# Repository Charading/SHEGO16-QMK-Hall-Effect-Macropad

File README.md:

# SHEGO16-QMK-Hall-Effect-Macropad
An RP2040-powered 4x4 15 key macropad with a knob on the top row, that runs custom QMK firmware that allows analogue hall effect sensors to work, also has SOCD, works with VIA and SignalRGB

### Features
- QMK Firmware
- VIA Compatible
- Hall effect (adjustable actuation also)
- SOCD (last input wins on A and D)
- Works with SignalRGB
- ST7735 TFT Screen *(currently disabled/broken due to complications and implementing another way)*
- Per-key RGB
- Ambient strip
- Custom keycodes to send to UART to control esp32 *(for tft screen on my future build)* etc
- Multiple GPIO broken out for testing purposes
- Blink LED on GPIO25

I cant find a Hall effect keyboard that i genuinely like that has all the features that i want so i thought to make one myself. Technically i am still in prototype phase for the 'endgame' board i yearn to have, this was a originally a little test board that I was making so I could figure out how to do firmware. I've been working months on end on this project with many pcbs and components surrounding me. The end goal is a 75% keyboard, knob, a tft screen that can play gifs, **north** facing RGB (my goodness i hate south facing), and magnetic switches with socd. Sadly I think it would be too difficult to create a software/web utility to control certain features of the board so thats why after weeks on end trying to build firmware from scratch with C, then scrapped that and tried Rust, then scrapped again and thought to use heavily edited qmk, i am now here.
For my big 75%, the screen will now be implemented by using an [ESP32 running a GIF decoder](https://github.com/Charading/ESP32-GIF-Player ) that accepts UART commands and it uses SD card for storage

Thankyou [riskable](https://github.com/riskable)  for your amazing resources and being my inspiration for this passion project. 

This was one of my first ever pcbs

I recommend using [this version](https://github.com/Charading/qmk_picosdk
) of qmk for easy building of firmware, i could not get pico/stdlib.h to be located at all with normal qmk_firmware :(.

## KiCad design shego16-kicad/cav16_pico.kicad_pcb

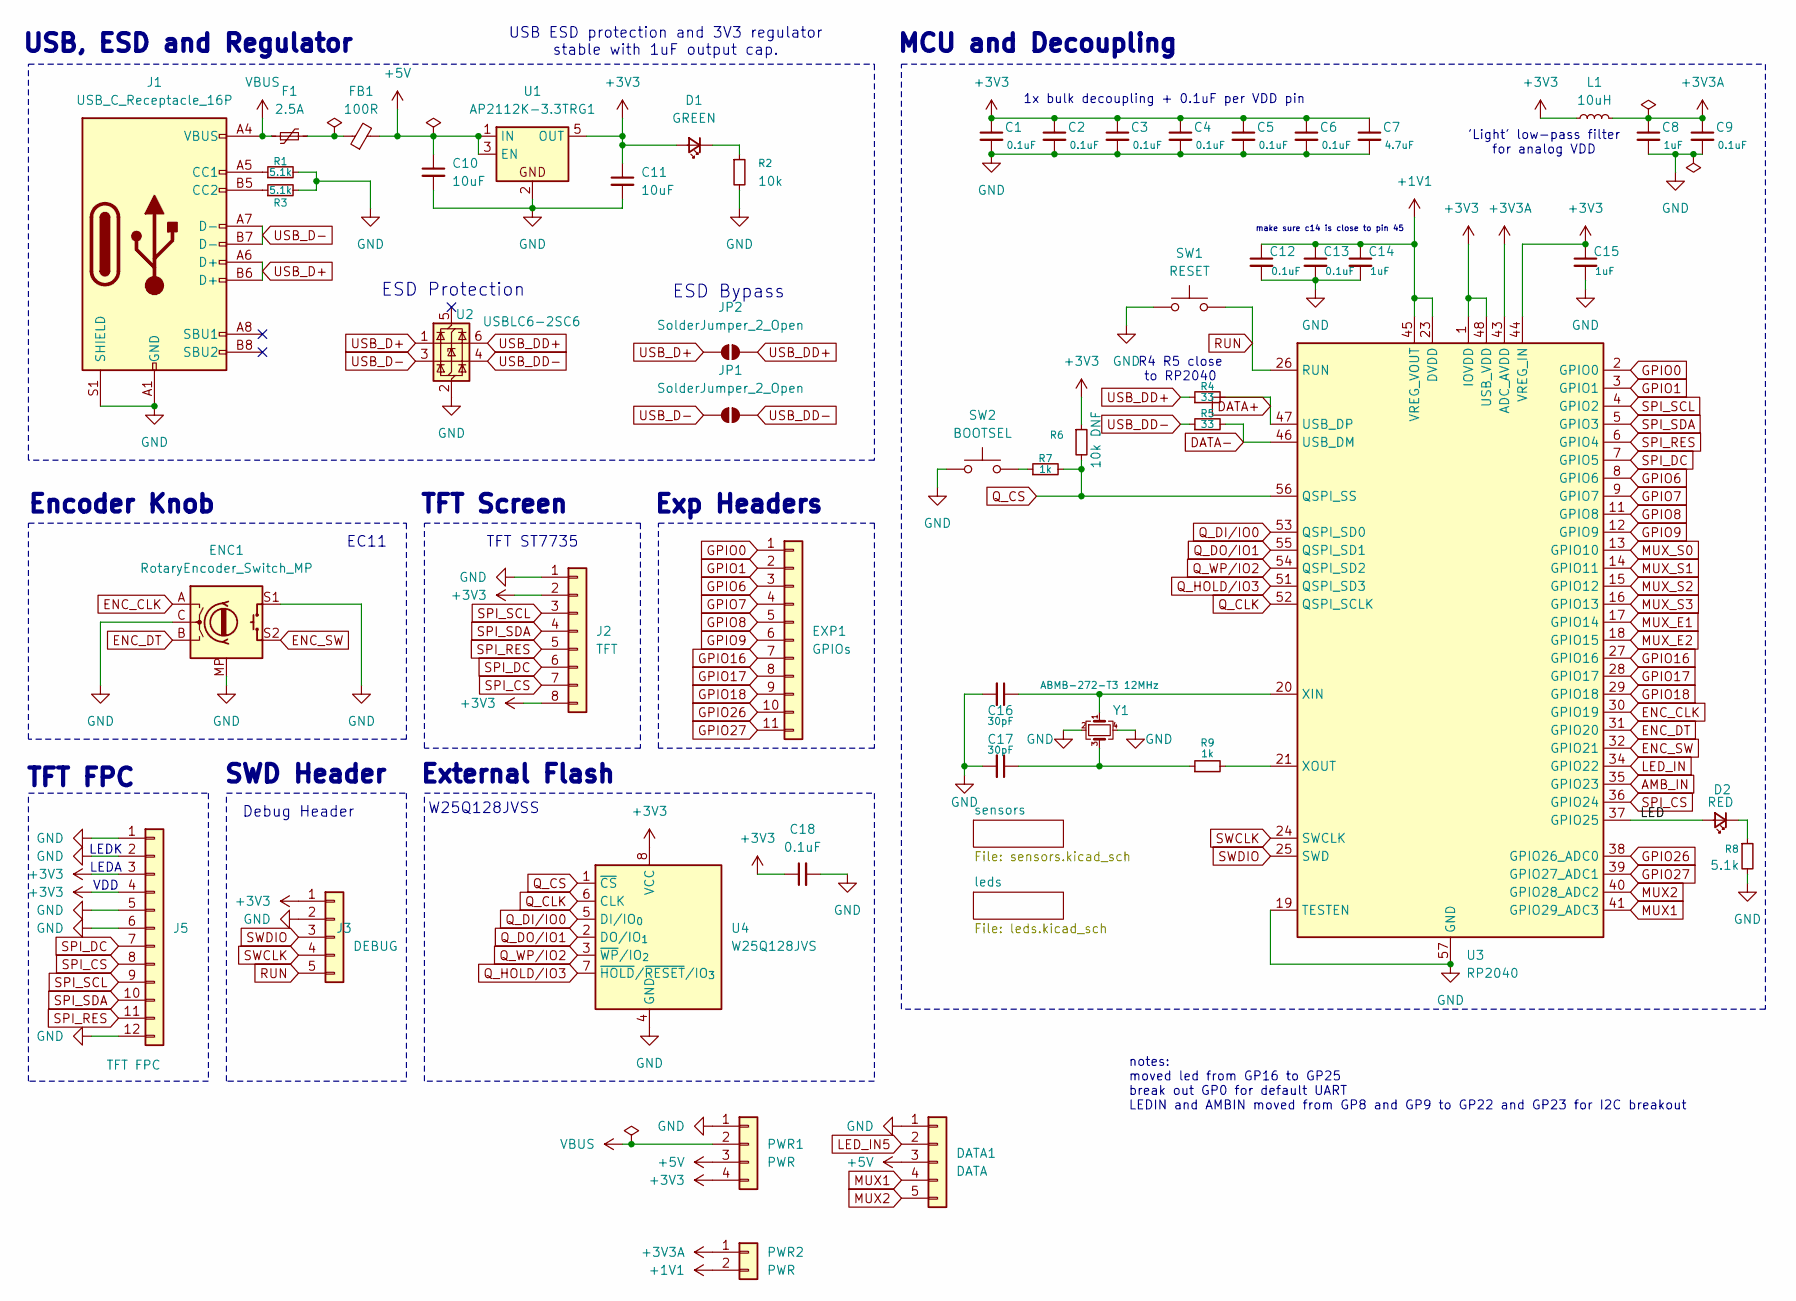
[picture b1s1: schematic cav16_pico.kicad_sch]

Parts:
C1, C2, C3, C4, C5, C6, C9, C12, C13, C18: 0.1uF; C_0402_1005Metric_Pad0.74x0.62mm_HandSolder
C7: 4.7uF; C_0805_2012Metric_Pad1.18x1.45mm_HandSolder
C8, C14, C15: 1uF; C_0402_1005Metric_Pad0.74x0.62mm_HandSolder
C10, C11: 10uF; C_0805_2012Metric_Pad1.18x1.45mm_HandSolder
C16, C17: 30pF; C_0402_1005Metric_Pad0.74x0.62mm_HandSolder
D1: GREEN; LED_0805_2012Metric_Pad1.15x1.40mm_HandSolder
D2: RED; LED_0805_2012Metric_Pad1.15x1.40mm_HandSolder
DATA1: DATA; PinHeader_1x05_P2.54mm_Vertical
ENC1: RotaryEncoder_Switch_MP; RotaryEncoder_Alps_EC11E-Switch_Vertical_H20mm_CircularMoun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
EXP1: GPIOs; PinHeader_1x11_P2.54mm_Vertical
F1: 2.5A; Fuse_1206_3216Metric_Pad1.42x1.75mm_BigPads
FB1: 100R; Ferrite_0805_2012Metric_Pad1.05x1.20mm_BigPads
J1: USB_C_Receptacle_16P; USB_C_Receptacle_HRO_TYPE-C-31-M-12
J2: TFT; PinHeader_1x08_P2.54mm_Vertical
J3: DEBUG; PinHeader_1x05_P2.54mm_Vertical
J5: TFT FPC; Hirose_FH12-12S-0.5SH_1x12-1MP_P0.50mm_Horizontal
JP1, JP2: SolderJumper_2_Open; SolderJumper-2_P1.3mm_Open_TrianglePad1.0x1.5mm
L1: 10uH; L_0805_2012Metric_Pad1.15x1.40mm_HandSolder
PWR1: PWR; PinHeader_1x04_P2.54mm_Vertical
PWR2: PWR; PinHeader_1x02_P2.54mm_Vertical
R1, R3: 5.1k; R_0603_1608Metric_Pad0.98x0.95mm_HandSolder
R2: 10k; R_0805_2012Metric_Pad1.20x1.40mm_HandSolder
R4, R5: 33; R_0805_2012Metric_Pad1.20x1.40mm_HandSolder
R6: 10k DNF; R_0603_1608Metric_Pad0.98x0.95mm_HandSolder
R7: 1k; R_0603_1608Metric_Pad0.98x0.95mm_HandSolder
R8: 5.1k; R_0805_2012Metric_Pad1.20x1.40mm_HandSolder
R9: 1k; C_0402_1005Metric_Pad0.74x0.62mm_HandSolder
SW1: RESET; SW_SPST_PTS810
SW2: BOOTSEL; SW_SPST_PTS810
U1: AP2112K-3.3TRG1; SOT-23-5
U2: USBLC6-2SC6; SOT-23-6
U3: RP2040; QFN-56-1EP_7x7mm_P0.4mm_EP3.2x3.2mm_ThermalVias
U4: W25Q128JVS; SOIC-8_5.3x5.3mm_P1.27mm
Y1: ABMB-272-T3 12MHz; Crystal_SMD_3225-4Pin_3.2x2.5mm_BigPads

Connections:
+1V1: C12.1, C13.1, C14.1, PWR2.2, U3.23 (DVDD), U3.45 (VREG_VOUT), U3.50 (DVDD)
+3V3: C1.1, C2.1, C3.1, C4.1, C5.1, C6.1, C7.1, C11.1, C15.1, C18.1, D1.2 (A), J2.2, J2.8, J3.1, J5.3, J5.4, L1.1, PWR1.4, R6.1, U1.5 (OUT), U3.1 (IOVDD), U3.10 (IOVDD), U3.22 (IOVDD), U3.33 (IOVDD), U3.42 (IOVDD), U3.44 (VREG_IN), U3.48 (USB_VDD), U3.49 (IOVDD), U4.8 (VCC); also elsewhere on the board
+3V3A: C8.1, C9.1, L1.2, PWR2.1, U3.43 (ADC_AVDD)
+5V: C10.1, DATA1.3, FB1.2, PWR1.3, U1.1 (IN), U1.3 (EN); also elsewhere on the board
/LED: D2.2 (A), U3.37 (GPIO25)
AMB_IN: U3.35 (GPIO23); also elsewhere on the board
DATA+: R4.2, U3.47 (USB_DP)
DATA-: R5.2, U3.46 (USB_DM)
ENC_CLK: ENC1.A, U3.30 (GPIO19)
ENC_DT: ENC1.B, U3.31 (GPIO20)
ENC_SW: ENC1.S2, U3.32 (GPIO21)
GND: C1.2, C2.2, C3.2, C4.2, C5.2, C6.2, C7.2, C8.2, C9.2, C10.2, C11.2, C12.2, C13.2, C14.2, C15.2, C16.2, C17.2, C18.2, DATA1.1, ENC1.C, ENC1.MP, ENC1.S1, J1.A1 (GND), J1.A12 (GND), J1.B1 (GND), J1.B12 (GND), J1.S1 (SHIELD), J2.1, J3.2, J5.1, J5.2, J5.5, J5.6, J5.12, J5.MP, PWR1.1, R1.2, R2.2, R3.2, R8.2, SW1.1, SW2.1, U1.2, U2.2 (GND), U3.19 (TESTEN), U3.57 (GND), U4.4 (GND), Y1.2, Y1.4; also elsewhere on the board
GPIO0: EXP1.1, U3.2 (GPIO0)
GPIO1: EXP1.2, U3.3 (GPIO1)
GPIO6: EXP1.3, U3.8 (GPIO6)
GPIO7: EXP1.4, U3.9 (GPIO7)
GPIO8: EXP1.5, U3.11 (GPIO8)
GPIO9: EXP1.6, U3.12 (GPIO9)
GPIO16: EXP1.7, U3.27 (GPIO16)
GPIO17: EXP1.8, U3.28 (GPIO17)
GPIO18: EXP1.9, U3.29 (GPIO18)
GPIO26: EXP1.10, U3.38 (GPIO26_ADC0)
GPIO27: EXP1.11, U3.39 (GPIO27_ADC1)
LED_IN: U3.34 (GPIO22); also elsewhere on the board
LED_IN5: DATA1.2; also elsewhere on the board
MUX1: DATA1.4, U3.41 (GPIO29_ADC3); also elsewhere on the board
MUX2: DATA1.5, U3.40 (GPIO28_ADC2); also elsewhere on the board
MUX_E1: U3.17 (GPIO14); also elsewhere on the board
MUX_E2: U3.18 (GPIO15); also elsewhere on the board
MUX_S0: U3.13 (GPIO10); also elsewhere on the board
MUX_S1: U3.14 (GPIO11); also elsewhere on the board
MUX_S2: U3.15 (GPIO12); also elsewhere on the board
MUX_S3: U3.16 (GPIO13); also elsewhere on the board
unnamed: C17.1, R9.1, Y1.3
unnamed: D1.1 (K), R2.1
unnamed: D2.1 (K), R8.1
unnamed: F1.2, FB1.1
unnamed: J1.A5 (CC1), R1.1
unnamed: J1.B5 (CC2), R3.1
unnamed: R7.1, SW2.2
unnamed: C16.1, U3.20 (XIN), Y1.1
unnamed: R9.2, U3.21 (XOUT)
Q_CLK: U3.52 (QSPI_SCLK), U4.6 (CLK)
Q_CS: R6.2, R7.2, U3.56 (QSPI_SS), U4.1 (~CS)
Q_DI/IO0: U3.53 (QSPI_SD0), U4.5 (DI/IO_{0})
Q_DO/IO1: U3.55 (QSPI_SD1), U4.2 (DO/IO_{1})
Q_HOLD/IO3: U3.51 (QSPI_SD3), U4.7 (~HOLD/~RESET/IO_{3})
Q_WP/IO2: U3.54 (QSPI_SD2), U4.3 (~WP/IO_{2})
RUN: J3.5, SW1.2, U3.26 (RUN)
SPI_CS: J2.7, J5.8, U3.36 (GPIO24)
SPI_DC: J2.6, J5.7, U3.7 (GPIO5)
SPI_RES: J2.5, J5.11, U3.6 (GPIO4)
SPI_SCL: J2.3, J5.9, U3.4 (GPIO2)
SPI_SDA: J2.4, J5.10, U3.5 (GPIO3)
SWCLK: J3.4, U3.24 (SWCLK)
SWDIO: J3.3, U3.25 (SWD)
USB_D+: J1.A6 (D+), J1.B6 (D+), JP2.1 (A), U2.1 (I/O1)
USB_D-: J1.A7 (D-), J1.B7 (D-), JP1.1 (A), U2.3 (I/O2)
USB_DD+: JP2.2 (B), R4.1, U2.6 (I/O1)
USB_DD-: JP1.2 (B), R5.1, U2.4 (I/O2)
VBUS: F1.1, J1.A4 (VBUS), J1.A9 (VBUS), J1.B4 (VBUS), J1.B9 (VBUS), PWR1.2

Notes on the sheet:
TFT Screen
LEDA
R4 R5 close to RP2040
notes: moved led from GP16 to GP25 break out GP0 for default UART LEDIN and AMBIN moved from GP8 and GP9 to GP22 and GP23 for I2C breakout
Encoder Knob
MCU and Decoupling
LEDK
External Flash
USB, ESD and Regulator
ESD Bypass
SWD Header
make sure c14 is close to pin 45
'Light' low-pass filter for analog VDD
Debug Header
VDD
Exp Headers
EC11
1x bulk decoupling + 0.1uF per VDD pin
TFT FPC
ESD Protection
USB ESD protection and 3V3 regulator stable with 1uF output cap.
TFT ST7735
W25Q128JVSS

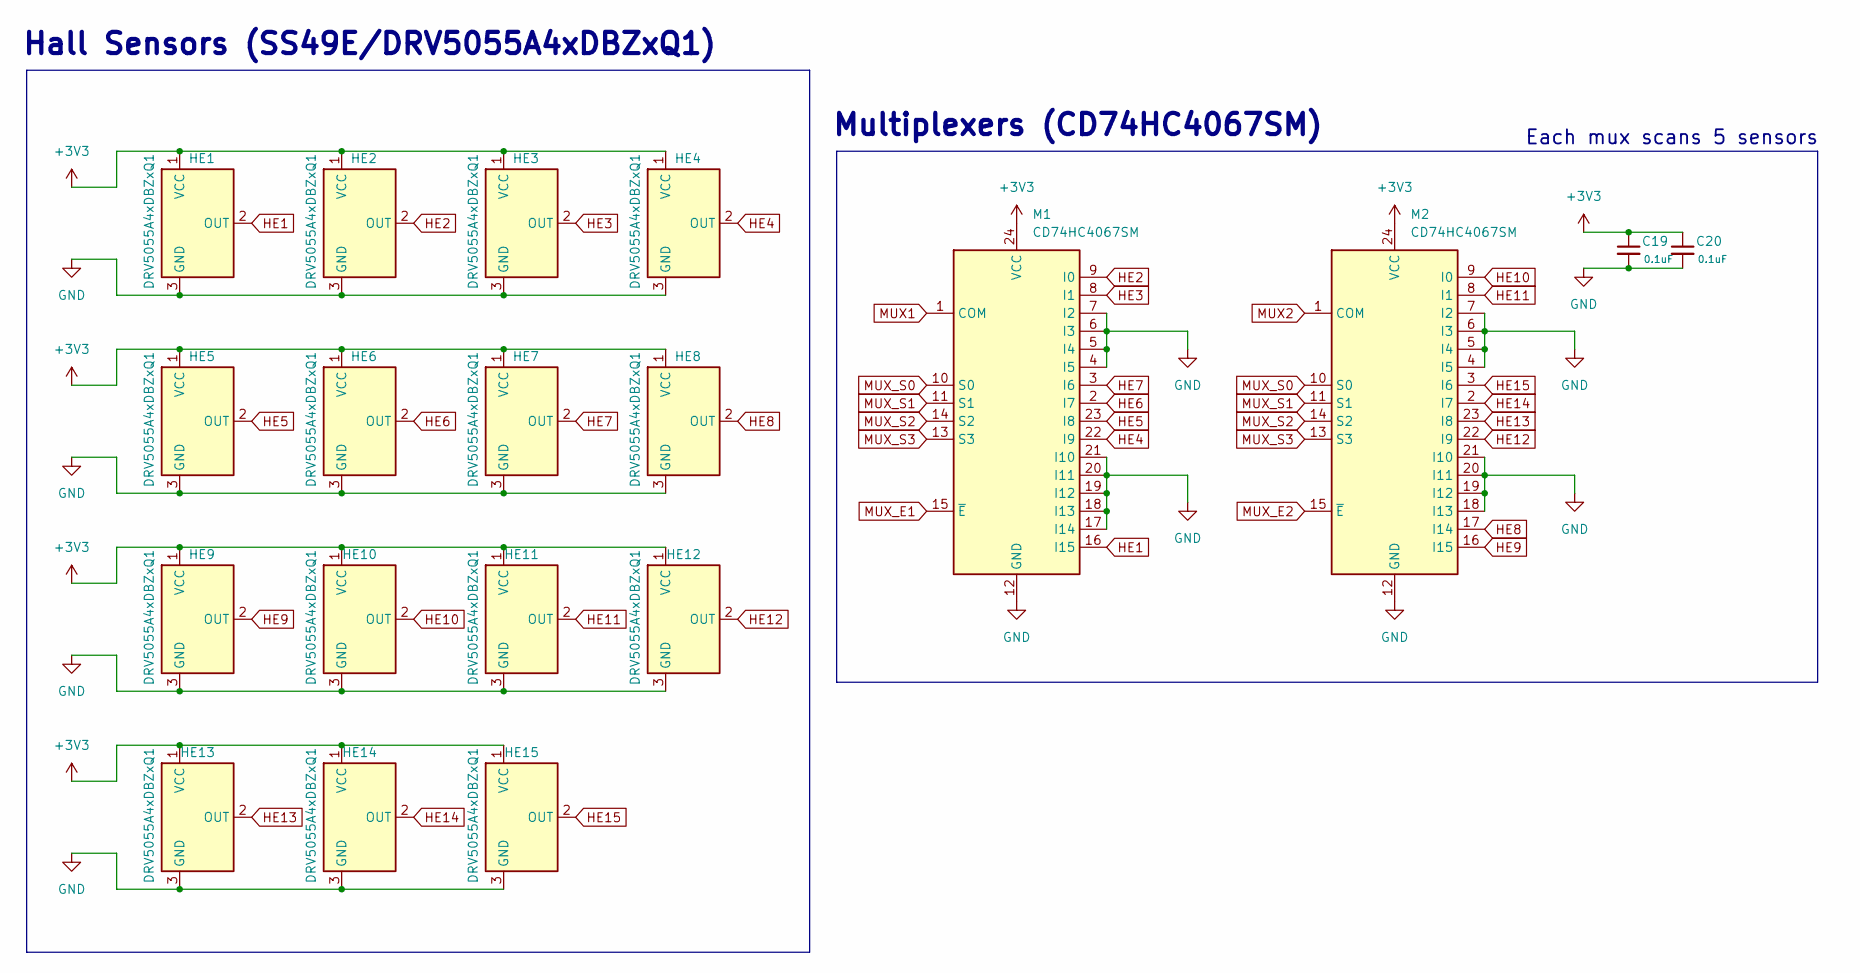
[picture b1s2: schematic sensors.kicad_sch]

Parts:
C19, C20: 0.1uF; C_0402_1005Metric_Pad0.74x0.62mm_HandSolder
HE1, HE2, HE3, HE4, HE5, HE6, HE7, HE8, HE9, HE10, HE11, HE12, HE13, HE14, HE15: DRV5055A4xDBZxQ1; SW_MX_HE_90deg_1u
M1, M2: CD74HC4067SM; SSOP-24_5.3x8.2mm_P0.65mm

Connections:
+3V3: C19.1, C20.1, HE1.1 (VCC), HE2.1 (VCC), HE3.1 (VCC), HE4.1 (VCC), HE5.1 (VCC), HE6.1 (VCC), HE7.1 (VCC), HE8.1 (VCC), HE9.1 (VCC), HE10.1 (VCC), HE11.1 (VCC), HE12.1 (VCC), HE13.1 (VCC), HE14.1 (VCC), HE15.1 (VCC), M1.24 (VCC), M2.24 (VCC); also elsewhere on the board
GND: C19.2, C20.2, HE1.3 (GND), HE2.3 (GND), HE3.3 (GND), HE4.3 (GND), HE5.3 (GND), HE6.3 (GND), HE7.3 (GND), HE8.3 (GND), HE9.3 (GND), HE10.3 (GND), HE11.3 (GND), HE12.3 (GND), HE13.3 (GND), HE14.3 (GND), HE15.3 (GND), M1.4 (I5), M1.5 (I4), M1.6 (I3), M1.7 (I2), M1.12 (GND), M1.17 (I14), M1.18 (I13), M1.19 (I12), M1.20 (I11), M1.21 (I10), M2.4 (I5), M2.5 (I4), M2.6 (I3), M2.7 (I2), M2.12 (GND), M2.18 (I13), M2.19 (I12), M2.20 (I11), M2.21 (I10); also elsewhere on the board
HE1: HE1.2 (OUT), M1.16 (I15)
HE2: HE2.2 (OUT), M1.9 (I0)
HE3: HE3.2 (OUT), M1.8 (I1)
HE4: HE4.2 (OUT), M1.22 (I9)
HE5: HE5.2 (OUT), M1.23 (I8)
HE6: HE6.2 (OUT), M1.2 (I7)
HE7: HE7.2 (OUT), M1.3 (I6)
HE8: HE8.2 (OUT), M2.17 (I14)
HE9: HE9.2 (OUT), M2.16 (I15)
HE10: HE10.2 (OUT), M2.9 (I0)
HE11: HE11.2 (OUT), M2.8 (I1)
HE12: HE12.2 (OUT), M2.22 (I9)
HE13: HE13.2 (OUT), M2.23 (I8)
HE14: HE14.2 (OUT), M2.2 (I7)
HE15: HE15.2 (OUT), M2.3 (I6)
MUX1: M1.1 (COM); also elsewhere on the board
MUX2: M2.1 (COM); also elsewhere on the board
MUX_E1: M1.15 (~E); also elsewhere on the board
MUX_E2: M2.15 (~E); also elsewhere on the board
MUX_S0: M1.10 (S0), M2.10 (S0); also elsewhere on the board
MUX_S1: M1.11 (S1), M2.11 (S1); also elsewhere on the board
MUX_S2: M1.14 (S2), M2.14 (S2); also elsewhere on the board
MUX_S3: M1.13 (S3), M2.13 (S3); also elsewhere on the board

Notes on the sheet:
Each mux scans 5 sensors
Multiplexers (CD74HC4067SM)
Hall Sensors (SS49E/DRV5055A4xDBZxQ1)

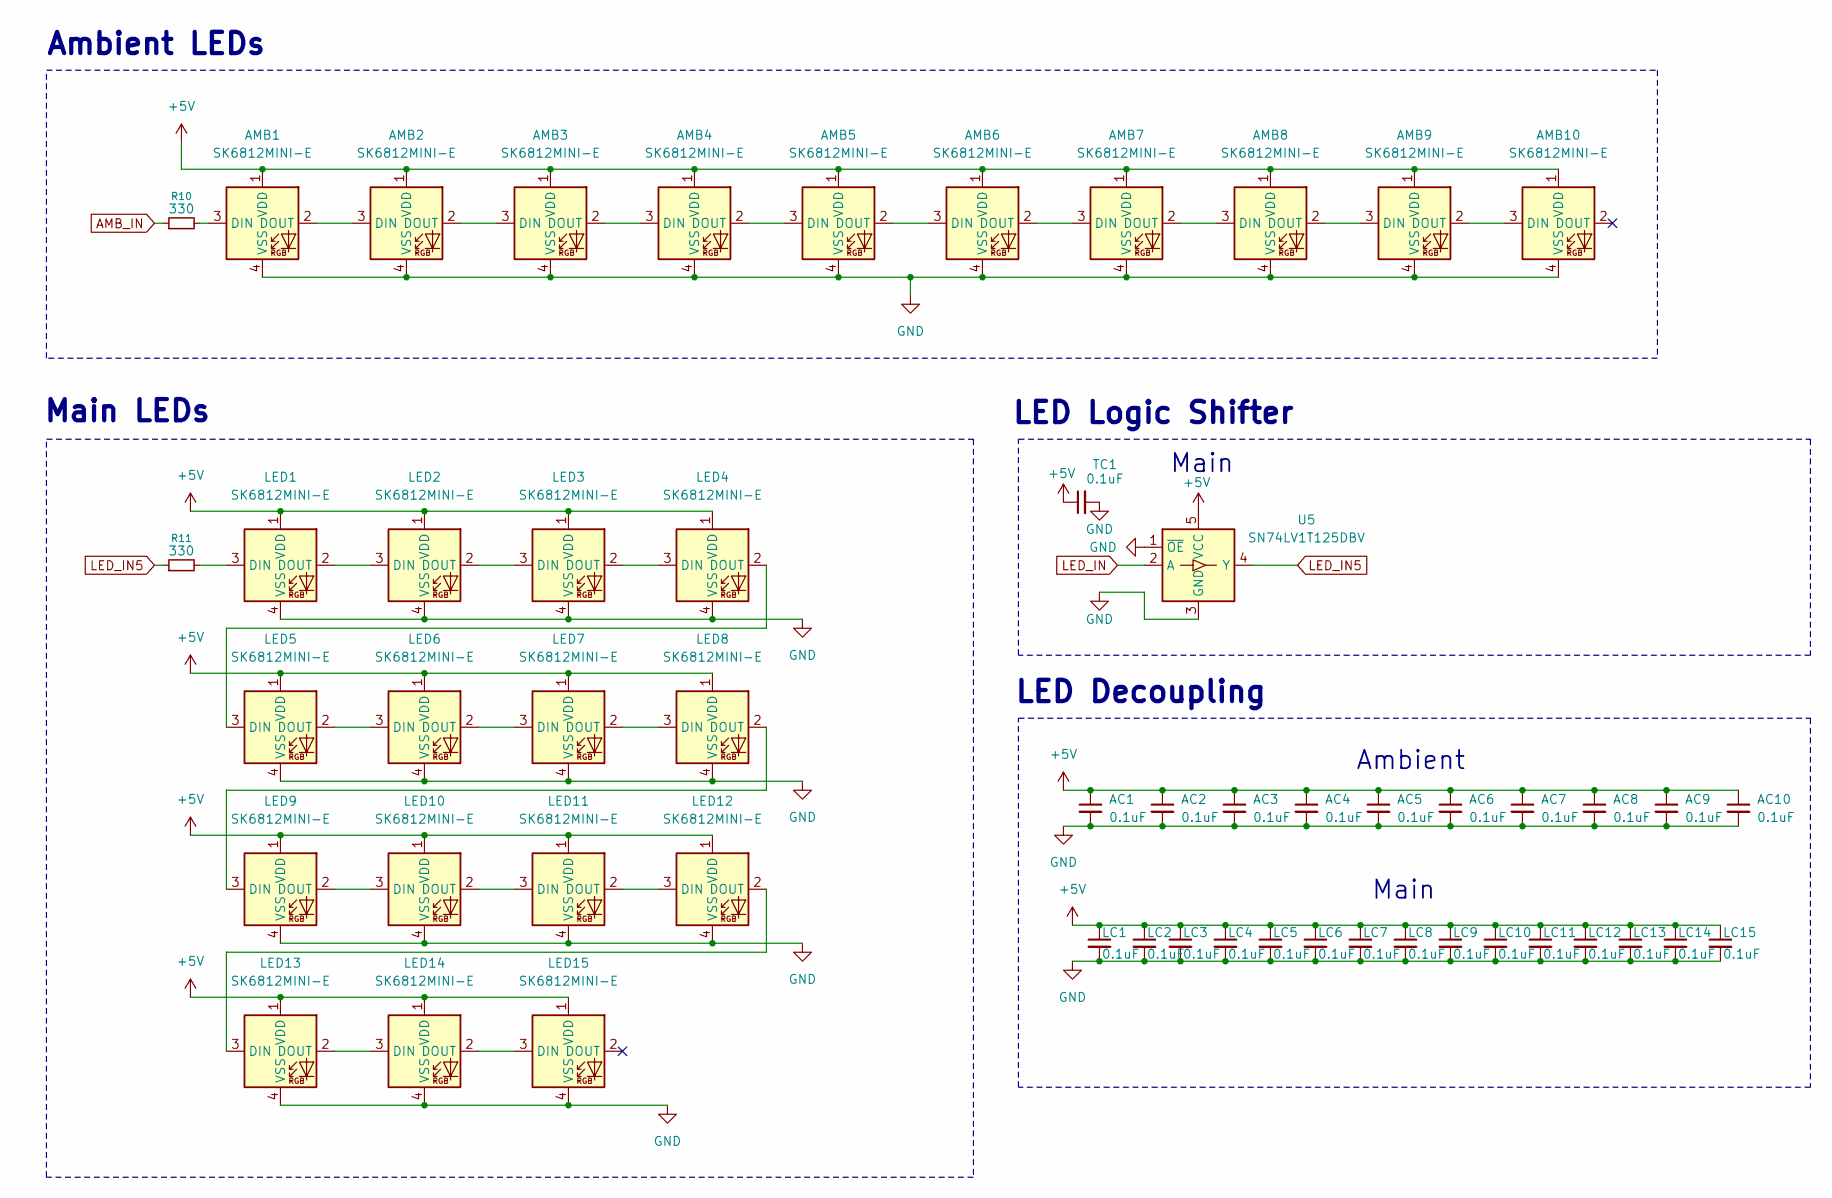
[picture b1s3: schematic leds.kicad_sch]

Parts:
AC1, AC2, AC3, AC4, AC5, AC6, AC7, AC8, AC9, AC10: 0.1uF; C_0805_2012Metric_Pad1.18x1.45mm_HandSolder
AMB1, AMB2, AMB3, AMB4, AMB5, AMB6, AMB7, AMB8, AMB9, AMB10: SK6812MINI-E; LED_6028R
LC1, LC2, LC3, LC4, LC5, LC6, LC7, LC8, LC9, LC10, LC11, LC12, LC13, LC14, LC15: 0.1uF; C_0805_2012Metric_Pad1.18x1.45mm_HandSolder
LED1, LED2, LED3, LED4, LED5, LED6, LED7, LED8, LED9, LED10, LED11, LED12, LED13, LED14, LED15: SK6812MINI-E; LED_6028R
R10, R11: 330; R_0603_1608Metric_Pad0.98x0.95mm_HandSolder
TC1: 0.1uF; C_0805_2012Metric_Pad1.18x1.45mm_HandSolder
U5: SN74LV1T125DBV; SOT-23-5

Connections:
+5V: AC1.1, AC2.1, AC3.1, AC4.1, AC5.1, AC6.1, AC7.1, AC8.1, AC9.1, AC10.1, AMB1.1 (VDD), AMB2.1 (VDD), AMB3.1 (VDD), AMB4.1 (VDD), AMB5.1 (VDD), AMB6.1 (VDD), AMB7.1 (VDD), AMB8.1 (VDD), AMB9.1 (VDD), AMB10.1 (VDD), LC1.1, LC2.1, LC3.1, LC4.1, LC5.1, LC6.1, LC7.1, LC8.1, LC9.1, LC10.1, LC11.1, LC12.1, LC13.1, LC14.1, LC15.1, LED1.1 (VDD), LED2.1 (VDD), LED3.1 (VDD), LED4.1 (VDD), LED5.1 (VDD), LED6.1 (VDD), LED7.1 (VDD), LED8.1 (VDD), LED9.1 (VDD), LED10.1 (VDD), LED11.1 (VDD), LED12.1 (VDD), LED13.1 (VDD), LED14.1 (VDD), LED15.1 (VDD), TC1.1, U5.5 (VCC); also elsewhere on the board
AMB_IN: R10.1; also elsewhere on the board
GND: AC1.2, AC2.2, AC3.2, AC4.2, AC5.2, AC6.2, AC7.2, AC8.2, AC9.2, AC10.2, AMB1.4 (VSS), AMB2.4 (VSS), AMB3.4 (VSS), AMB4.4 (VSS), AMB5.4 (VSS), AMB6.4 (VSS), AMB7.4 (VSS), AMB8.4 (VSS), AMB9.4 (VSS), AMB10.4 (VSS), LC1.2, LC2.2, LC3.2, LC4.2, LC5.2, LC6.2, LC7.2, LC8.2, LC9.2, LC10.2, LC11.2, LC12.2, LC13.2, LC14.2, LC15.2, LED1.4 (VSS), LED2.4 (VSS), LED3.4 (VSS), LED4.4 (VSS), LED5.4 (VSS), LED6.4 (VSS), LED7.4 (VSS), LED8.4 (VSS), LED9.4 (VSS), LED10.4 (VSS), LED11.4 (VSS), LED12.4 (VSS), LED13.4 (VSS), LED14.4 (VSS), LED15.4 (VSS), TC1.2, U5.1 (~OE), U5.3 (GND); also elsewhere on the board
LED_IN: U5.2 (A); also elsewhere on the board
LED_IN5: R11.1, U5.4 (Y); also elsewhere on the board
unnamed: AMB1.3 (DIN), R10.2
unnamed: AMB1.2 (DOUT), AMB2.3 (DIN)
unnamed: AMB2.2 (DOUT), AMB3.3 (DIN)
unnamed: AMB3.2 (DOUT), AMB4.3 (DIN)
unnamed: AMB4.2 (DOUT), AMB5.3 (DIN)
unnamed: AMB5.2 (DOUT), AMB6.3 (DIN)
unnamed: AMB6.2 (DOUT), AMB7.3 (DIN)
unnamed: AMB7.2 (DOUT), AMB8.3 (DIN)
unnamed: AMB8.2 (DOUT), AMB9.3 (DIN)
unnamed: AMB9.2 (DOUT), AMB10.3 (DIN)
unnamed: LED1.3 (DIN), R11.2
unnamed: LED1.2 (DOUT), LED2.3 (DIN)
unnamed: LED2.2 (DOUT), LED3.3 (DIN)
unnamed: LED3.2 (DOUT), LED4.3 (DIN)
unnamed: LED4.2 (DOUT), LED5.3 (DIN)
unnamed: LED5.2 (DOUT), LED6.3 (DIN)
unnamed: LED6.2 (DOUT), LED7.3 (DIN)
unnamed: LED7.2 (DOUT), LED8.3 (DIN)
unnamed: LED8.2 (DOUT), LED9.3 (DIN)
unnamed: LED9.2 (DOUT), LED10.3 (DIN)
unnamed: LED10.2 (DOUT), LED11.3 (DIN)
unnamed: LED11.2 (DOUT), LED12.3 (DIN)
unnamed: LED12.2 (DOUT), LED13.3 (DIN)
unnamed: LED13.2 (DOUT), LED14.3 (DIN)
unnamed: LED14.2 (DOUT), LED15.3 (DIN)

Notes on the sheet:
Main
Ambient LEDs
Main LEDs
Ambient
LED Logic Shifter
LED Decoupling

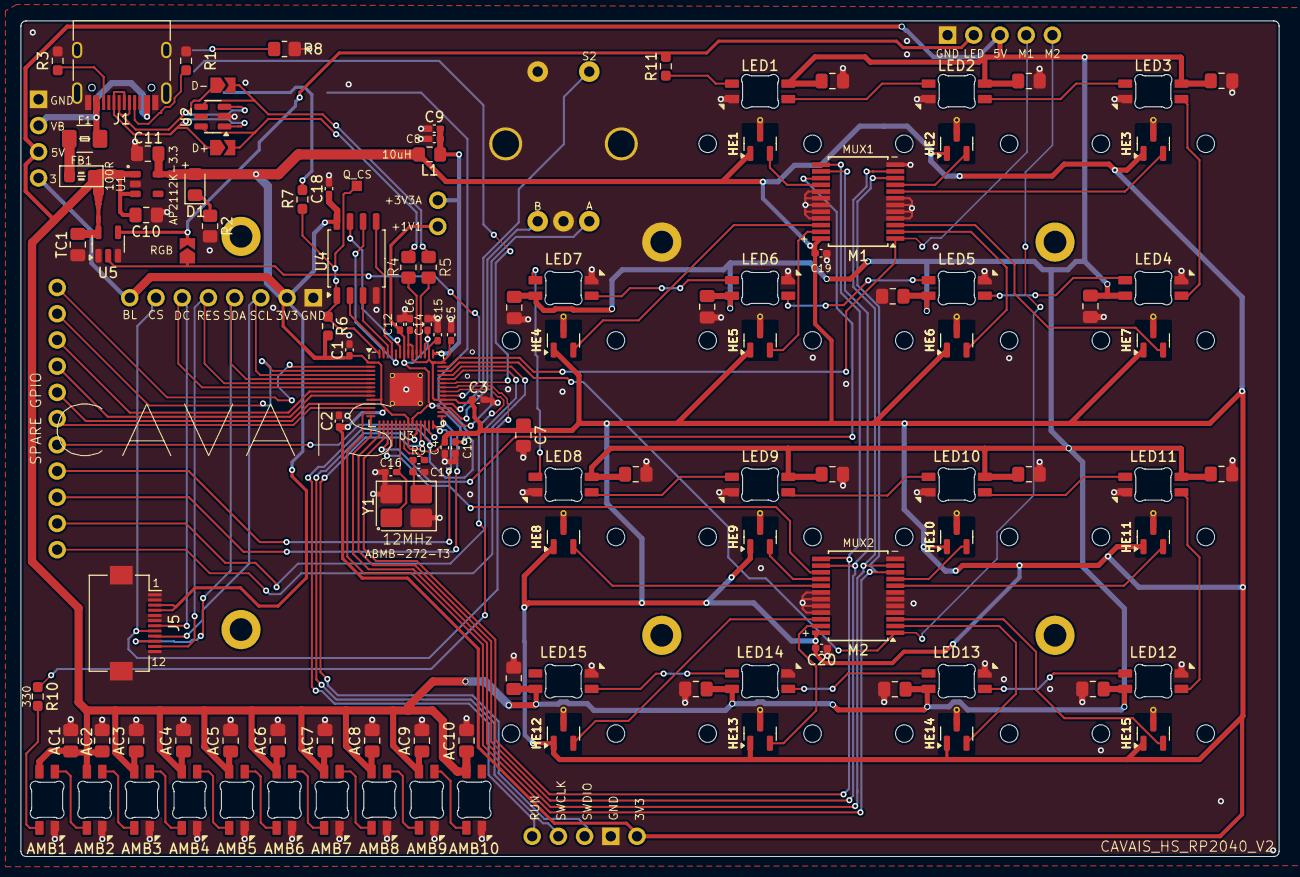
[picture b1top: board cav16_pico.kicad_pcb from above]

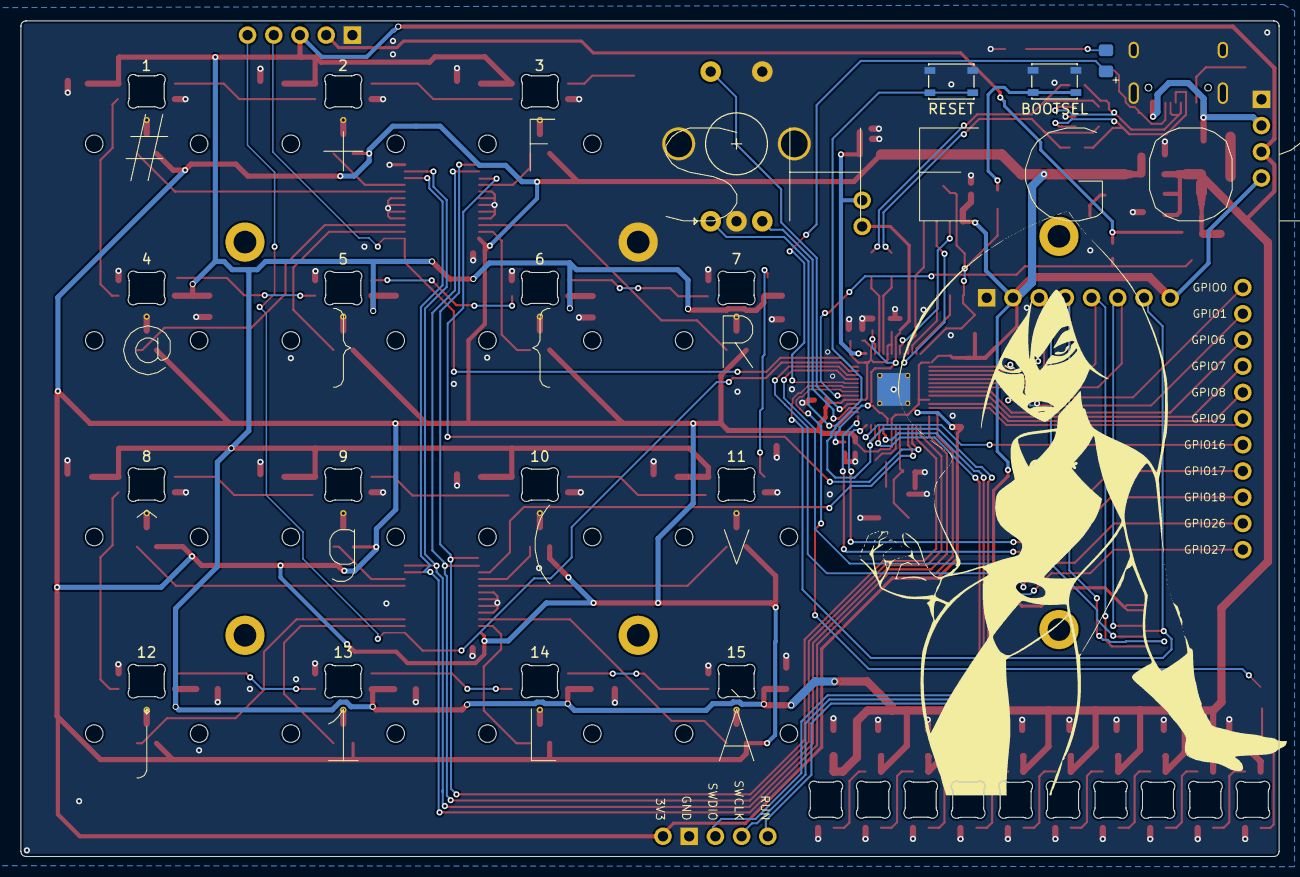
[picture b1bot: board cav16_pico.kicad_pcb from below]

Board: 2 copper layers, 121.9 x 80.9 mm, 124 parts (10 on the bottom side), 101 nets.

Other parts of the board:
RGB: SolderJumper-2_P1.3mm_Open_TrianglePad1.0x1.5mm

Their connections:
LED_IN: RGB.1; also elsewhere on the board
LED_IN5: RGB.2; also elsewhere on the board

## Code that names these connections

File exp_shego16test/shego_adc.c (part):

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#include "print.h"

// MUX control pins
#define MUX_S0 GP10
#define MUX_S1 GP11
#define MUX_S2 GP12
#define MUX_S3 GP13
#define MUX1_EN GP14
#define MUX2_EN GP15
#define MUX1_ADC_PIN GP29
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    uint16_t keycode;
} key_mapping_t;

// MUX1 channel mappings
static const key_mapping_t mux1_keys[16] = {
    {0, 1, KC_2},   // CH0 -> he2 -> "2"
    {0, 0, KC_1},   // CH1 -> he3 -> "1" 
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    {0, 2, KC_3}    // CH15 -> he1 -> "3"
};

// MUX2 channel mappings
static const key_mapping_t mux2_keys[16] = {
    {2, 1, KC_S},   // CH0 -> he10 -> "S"
    {2, 0, KC_A},   // CH1 -> he11 -> "A"
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}

static void select_mux_channel(uint8_t channel) {
    writePin(MUX_S0, (channel & 0x01) ? 1 : 0);
    writePin(MUX_S1, (channel & 0x02) ? 1 : 0);
    writePin(MUX_S2, (channel & 0x04) ? 1 : 0);
    writePin(MUX_S3, (channel & 0x08) ? 1 : 0);
    wait_us(50);
}

void matrix_init_custom(void) {
    // Setup MUX control pins
    setPinOutput(MUX_S0);
    setPinOutput(MUX_S1);
    setPinOutput(MUX_S2);
    setPinOutput(MUX_S3);
    setPinOutput(MUX1_EN);
    setPinOutput(MUX2_EN);
    
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        select_mux_channel(ch);
        
        // Read MUX1
        writePinLow(MUX1_EN);   // Enable MUX1
        writePinHigh(MUX2_EN);  // Disable MUX2
        wait_us(100);
        
        uint16_t adc1 = read_adc_pin(MUX1_ADC_PIN);
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        }
        
        // Read MUX2
        writePinHigh(MUX1_EN);  // Disable MUX1
        writePinLow(MUX2_EN);   // Enable MUX2
        wait_us(100);
        
        uint16_t adc2 = read_adc_pin(MUX2_ADC_PIN);
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
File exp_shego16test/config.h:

#pragma once

// Rotary encoder - CLK19, DT20, SW21

// RGB Matrix - 15 LEDs (no LED at encoder position [0,3], 10 Ambient LEDs)
#define WS2812_DI_PIN GP22
#define RGB_MATRIX_LED_COUNT 25

// Underglow - 10 ambient LEDs on GP9  
// #define RGBLIGHT_LED_COUNT 10
// #define WS2812_DI_PIN_RGBLIGHT GP9

#define DRIVER_LED_TOTAL 25

// Split configuration
#define WS2812_LED_COUNT_1 15  // Per-key LEDs on GP8
#define WS2812_LED_COUNT_2 10  // Ambient LEDs on GP9

#define MATRIX_ROWS 4
#define MATRIX_COLS 4

// RGB Matrix configuration (for per-key LEDs)

#define RGB_MATRIX_KEYPRESSES
#define RGB_MATRIX_KEYRELEASES
#define RGB_MATRIX_FRAMEBUFFER_EFFECTS

// Underglow configuration
#define RGBLIGHT_EFFECT_BREATHING
#define RGBLIGHT_EFFECT_RAINBOW_MOOD
#define RGBLIGHT_EFFECT_RAINBOW_SWIRL
#define RGBLIGHT_EFFECT_SNAKE
#define RGBLIGHT_EFFECT_KNIGHT
#define RGBLIGHT_EFFECT_CHRISTMAS
#define RGBLIGHT_EFFECT_STATIC_GRADIENT
#define RGBLIGHT_EFFECT_RGB_TEST
#define RGBLIGHT_EFFECT_ALTERNATING
#define RGBLIGHT_EFFECT_TWINKLE

// ST7735 SPI pin configuration (ensure these match your wiring)
#ifndef SPI_SCK
#define SPI_SCK GP2
#endif
#ifndef SPI_MOSI
#define SPI_MOSI GP3
#endif
#ifndef SPI_RES
#define SPI_RES GP4
#endif
#ifndef SPI_DC
#define SPI_DC GP5
#endif
#ifndef SPI_CS
#define SPI_CS GP24
#endif

// Display dimensions (ST7735R 128x128 panel)
#ifndef SPI_WIDTH
#define SPI_WIDTH 128
#endif
#ifndef SPI_HEIGHT
#define SPI_HEIGHT 128
#endif

// Debounce and performance
#define DEBOUNCE 5
#define USB_POLLING_INTERVAL_MS 1

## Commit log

2025-09-26 Enhance README with project details and features
    Expanded the README to include additional features and personal project insights.
2025-09-26 Update README with ESP32 GIF player details
    Added information about the ESP32 implementation for the screen.
2025-09-26 Fix typos and format links in README.md
    Corrected typos and improved formatting in README.
2025-09-26 Add files via upload
    the SignalRGB plugin for the board
2025-09-26 Add files via upload
    firmware for board
